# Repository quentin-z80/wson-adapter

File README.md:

# wson-adapter

WSON8 6x8mm to 6x5mm Adapter PCB

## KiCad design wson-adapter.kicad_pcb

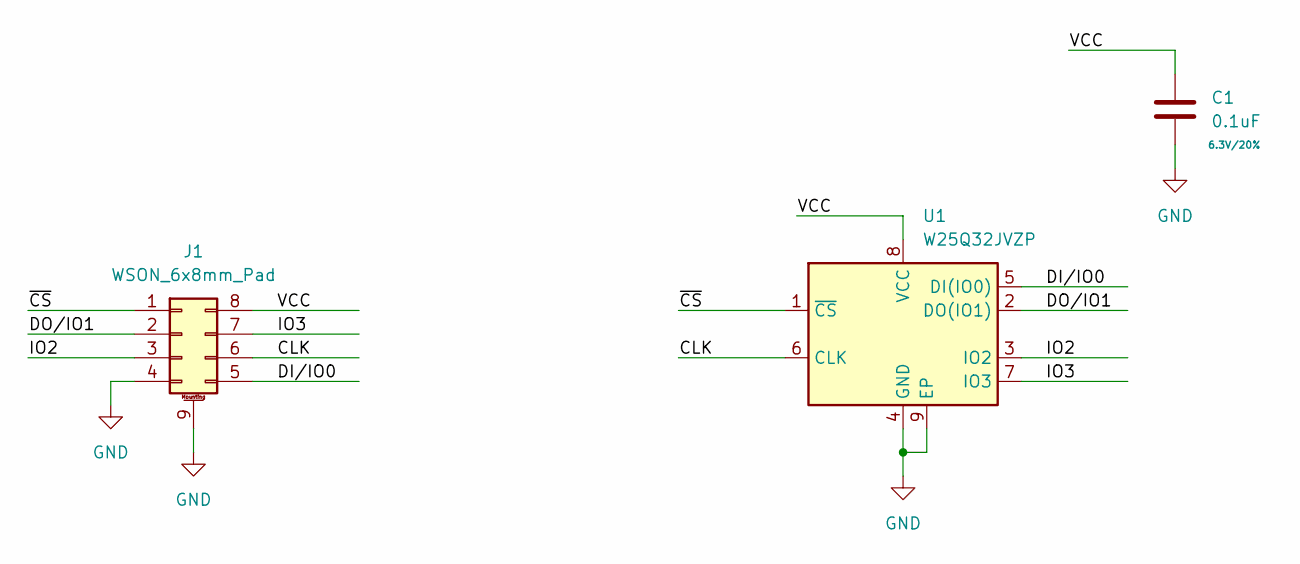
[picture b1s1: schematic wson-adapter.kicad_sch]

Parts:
C1: 0.1uF; C_0201_0603Metric; Rating 6.3V/20%
J1: WSON_6x8mm_Pad; WSON8_6x8mm_Pad
U1: W25Q32JVZP; WSON-8-1EP_6x5mm_P1.27mm_EP3.4x4.3mm

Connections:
/CLK: J1.6, U1.6 (CLK)
/DI/IO0: J1.5, U1.5 (DI(IO0))
/DO/IO1: J1.2, U1.2 (DO(IO1))
/IO2: J1.3, U1.3 (IO2)
/IO3: J1.7, U1.7 (IO3)
/VCC: C1.1, J1.8, U1.8 (VCC)
/~CS: J1.1, U1.1 (~CS)
GND: C1.2, J1.4, J1.9 (EPAD), U1.4 (GND), U1.9 (EP)

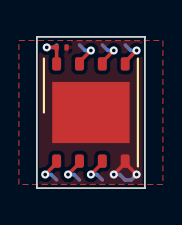
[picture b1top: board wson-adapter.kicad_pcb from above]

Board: 4 copper layers, 6.0 x 8.4 mm, 3 parts (1 on the bottom side), 8 nets.

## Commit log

2022-08-01 inital commit
2022-08-01 add README
2022-08-02 add UNLICENSE
